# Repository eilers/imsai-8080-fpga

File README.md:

# S-100 compatible Computer

This project contains a full S-100 bus compliant micro computer based on the IMSAI-8080 design (which is basically a clone of the Altair 8800).
But instead of using old and hard to find computer parts, we use FPGAs to emulate their behavior.

**Please note:** This project is work in process! So please do not expect anything working for now.

This project contains the following components:

## S-100 Backplane (Motherboard)

The PCB here was not tested or used. I just ordered the board from [SmallRun](https://smallrun.net/shop/retrodisks/9-slot-s100-motherboard-with-integrated-power).
The Source of this version can be found on [GitHub](https://github.com/nullvalue0/S100MotherboardV5)

See folder `./S100MotherboardV5`

## S-100 Front Panel (CP-A)

This was also taken from [s100Computers](https://www.s100computers.com/My%20System%20Pages/FP%20Board/FP%20Board.htm) and cleaned to work with KiCad V10.

See folder `./S100-front-panel`

**Note:** This is not the design of the original CP-A provided by IMSAI in 1975. This one confirms the IEEE 696 and therefore works a bit different.

## IMSAI Front Panel (CP-A)

This is created from the original schmatics by IMSAI MPU-A REV.A 2/76.
In order to get a working reference, I decided to order the full front panel from [parastream.com](https://www.parastream.com/imsai/boards/cp-a-r.aspx) that belongs to the design here.

Important: This design is not fully IEEE 696 compatible without modifications as documented on the web page. Our Bus Master board is compatible to IMSAI and IEEE 696 if you select the correct FPGA core for it.

See folder `./imsai_cp-a`

## Bus Master

This is my work. The idea is to use only level shifters in order to connect a FPGA directly to the S-100 bus. All kind of S-100 boards that behave as bus master can therefore be recreated just be replacing the FPGA code. The first approach is to run a full IMSAI CPU board (MPU-A) on this board.
This board uses the [TE0725-04-21C-1-A](https://www.trenz-electronic.de/de/FPGA-Modul-mit-AMD-Artix-7A15T-1C-2-x-50-Pin-Header-3-5-x-7-3-cm/TE0725-04-21C-1-A) from Trenz, based on the AMD Artix™ 7A15T-1C.

See folder `./s100-bus-master`

The first FPGA implementation can be found in the folder `./s100-bus-master-fpga`. This code only contains some test code for debugging the S100 bus.

## References

* https://www.s100computers.com/index.html
* https://www.retrotechnology.com/herbs_stuff/s100.html
* https://github.com/nullvalue0/S100MotherboardV5

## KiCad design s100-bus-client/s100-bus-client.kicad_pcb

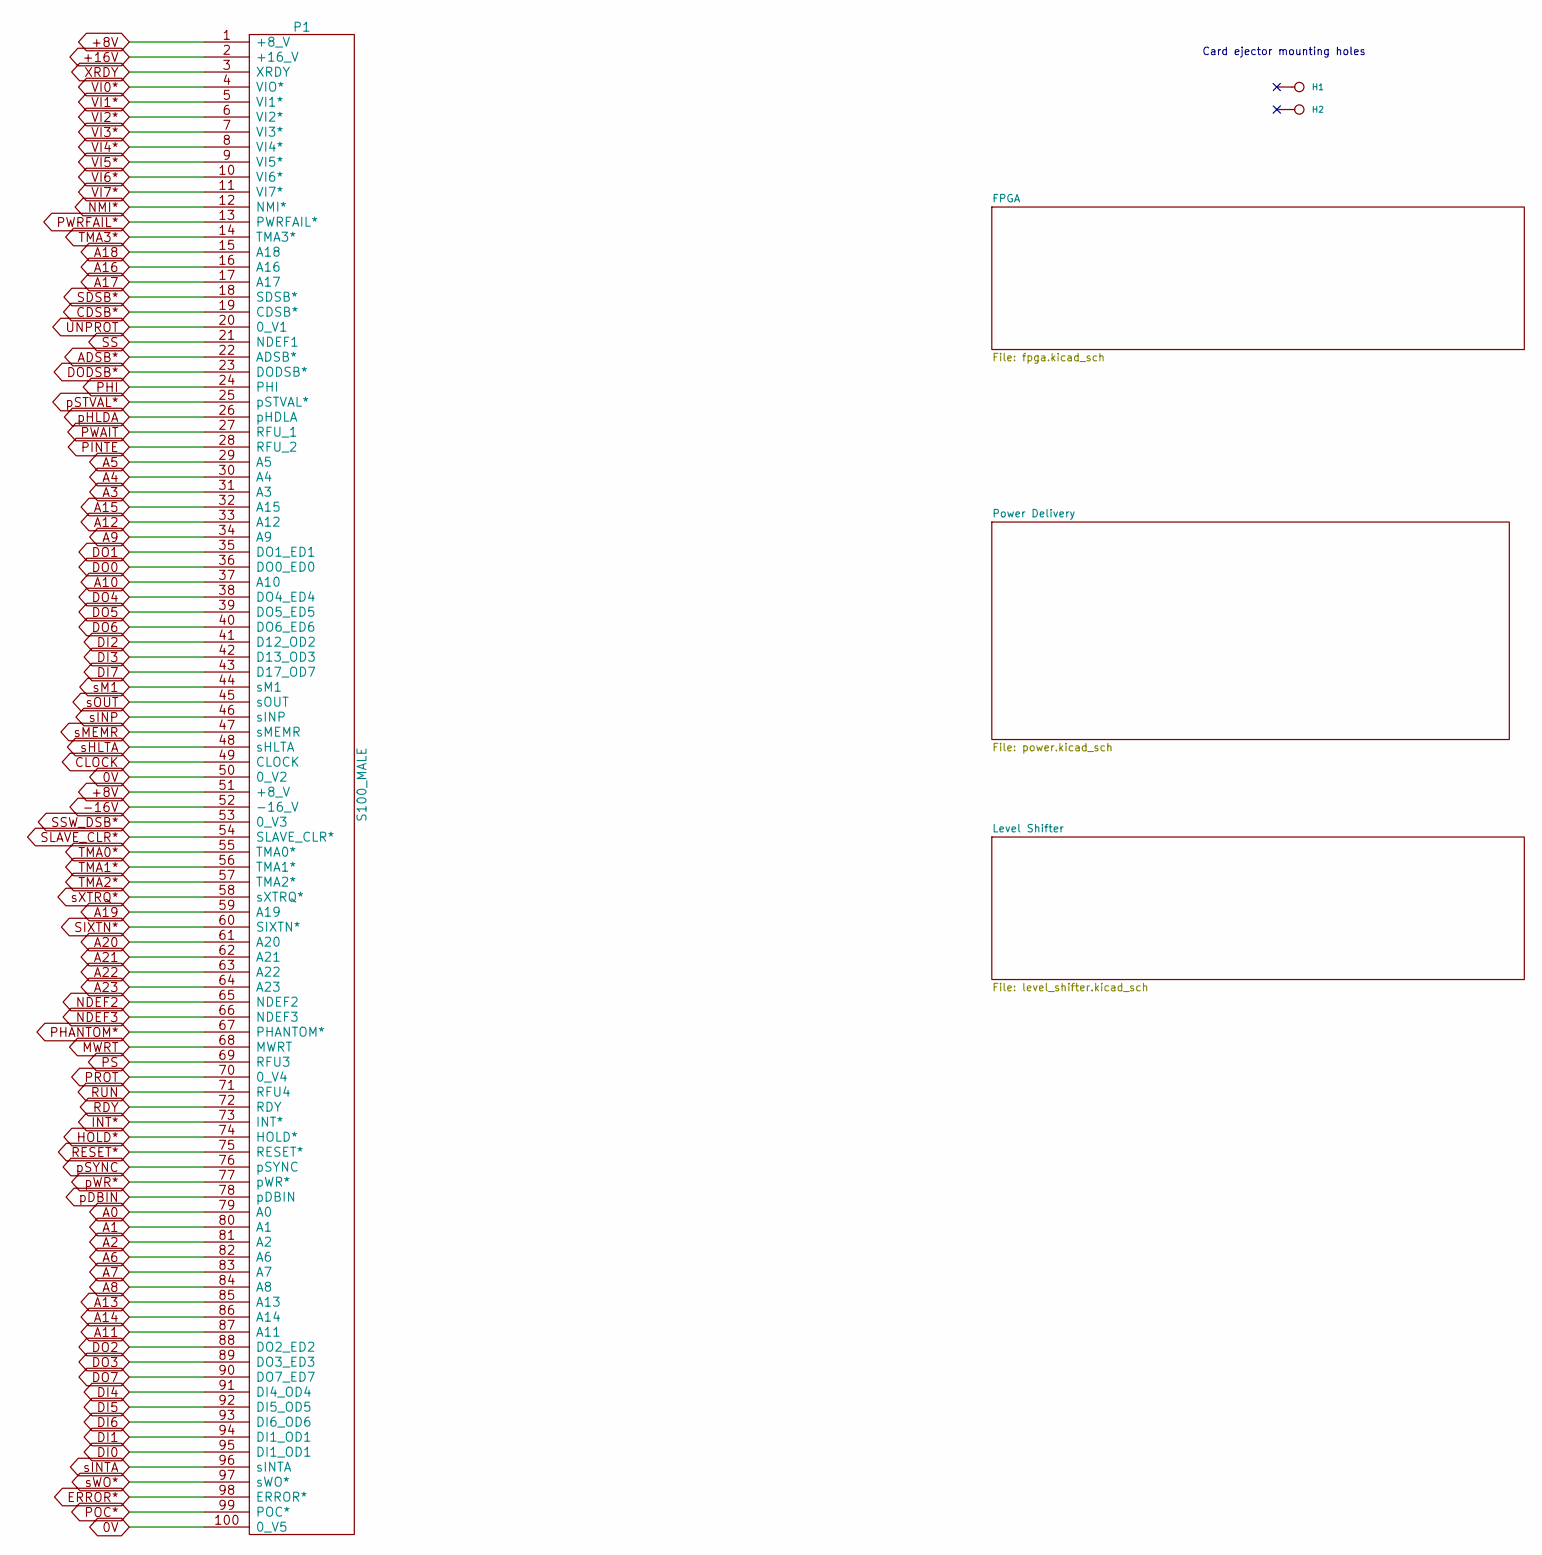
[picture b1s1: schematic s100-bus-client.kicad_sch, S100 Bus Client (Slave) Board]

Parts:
H1, H2: Ejector; s100-ejector
P1: S100_MALE; s100-edge-connector-male

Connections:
0V: P1.50 (0_V2), P1.100 (0_V5); also elsewhere on the board
+8V: P1.1 (+8_V), P1.51 (+8_V); also elsewhere on the board
+16V: P1.2 (+16_V)
-16V: P1.52 (-16_V)
A0: P1.79 (A0); also elsewhere on the board
A1: P1.80 (A1); also elsewhere on the board
A2: P1.81 (A2); also elsewhere on the board
A3: P1.31 (A3); also elsewhere on the board
A4: P1.30 (A4); also elsewhere on the board
A5: P1.29 (A5); also elsewhere on the board
A6: P1.82 (A6); also elsewhere on the board
A7: P1.83 (A7); also elsewhere on the board
A8: P1.84 (A8); also elsewhere on the board
A9: P1.34 (A9); also elsewhere on the board
A10: P1.37 (A10); also elsewhere on the board
A11: P1.87 (A11); also elsewhere on the board
A12: P1.33 (A12); also elsewhere on the board
A13: P1.85 (A13); also elsewhere on the board
A14: P1.86 (A14); also elsewhere on the board
A15: P1.32 (A15); also elsewhere on the board
A16: P1.16 (A16); also elsewhere on the board
A17: P1.17 (A17); also elsewhere on the board
A18: P1.15 (A18); also elsewhere on the board
A19: P1.59 (A19); also elsewhere on the board
A20: P1.61 (A20); also elsewhere on the board
A21: P1.62 (A21); also elsewhere on the board
A22: P1.63 (A22); also elsewhere on the board
A23: P1.64 (A23); also elsewhere on the board
ADSB*: P1.22 (ADSB*)
CDSB*: P1.19 (CDSB*)
CLOCK: P1.49 (CLOCK)
DI0: P1.95 (DI1_OD1); also elsewhere on the board
DI1: P1.94 (DI1_OD1); also elsewhere on the board
DI2: P1.41 (D12_OD2); also elsewhere on the board
DI3: P1.42 (D13_OD3); also elsewhere on the board
DI4: P1.91 (DI4_OD4); also elsewhere on the board
DI5: P1.92 (DI5_OD5); also elsewhere on the board
DI6: P1.93 (DI6_OD6); also elsewhere on the board
DI7: P1.43 (D17_OD7); also elsewhere on the board
DO0: P1.36 (DO0_ED0); also elsewhere on the board
DO1: P1.35 (DO1_ED1); also elsewhere on the board
DO2: P1.88 (DO2_ED2); also elsewhere on the board
DO3: P1.89 (DO3_ED3); also elsewhere on the board
DO4: P1.38 (DO4_ED4); also elsewhere on the board
DO5: P1.39 (DO5_ED5); also elsewhere on the board
DO6: P1.40 (DO6_ED6); also elsewhere on the board
DO7: P1.90 (DO7_ED7); also elsewhere on the board
DODSB*: P1.23 (DODSB*)
ERROR*: P1.98 (ERROR*)
HOLD*: P1.74 (HOLD*)
INT*: P1.73 (INT*)
MWRT: P1.68 (MWRT)
NDEF2: P1.65 (NDEF2)
NDEF3: P1.66 (NDEF3)
NMI*: P1.12 (NMI*)
PHANTOM*: P1.67 (PHANTOM*)
PHI: P1.24 (PHI)
PINTE: P1.28 (RFU_2)
POC*: P1.99 (POC*); also elsewhere on the board
PROT: P1.70 (0_V4)
PS: P1.69 (RFU3)
PWAIT: P1.27 (RFU_1)
PWRFAIL*: P1.13 (PWRFAIL*)
RDY: P1.72 (RDY)
RESET*: P1.75 (RESET*); also elsewhere on the board
RUN: P1.71 (RFU4)
SDSB*: P1.18 (SDSB*)
SIXTN*: P1.60 (SIXTN*)
SLAVE_CLR*: P1.54 (SLAVE_CLR*)
SS: P1.21 (NDEF1)
SSW_DSB*: P1.53 (0_V3)
TMA0*: P1.55 (TMA0*)
TMA1*: P1.56 (TMA1*)
TMA2*: P1.57 (TMA2*)
TMA3*: P1.14 (TMA3*)
UNPROT: P1.20 (0_V1)
VI0*: P1.4 (VIO*)
VI1*: P1.5 (VI1*)
VI2*: P1.6 (VI2*)
VI3*: P1.7 (VI3*)
VI4*: P1.8 (VI4*)
VI5*: P1.9 (VI5*)
VI6*: P1.10 (VI6*)
VI7*: P1.11 (VI7*)
XRDY: P1.3 (XRDY)
pDBIN: P1.78 (pDBIN); also elsewhere on the board
pHLDA: P1.26 (pHDLA)
pSTVAL*: P1.25 (pSTVAL*)
pSYNC: P1.76 (pSYNC)
pWR*: P1.77 (pWR*); also elsewhere on the board
sHLTA: P1.48 (sHLTA)
sINP: P1.46 (sINP)
sINTA: P1.96 (sINTA)
sM1: P1.44 (sM1)
sMEMR: P1.47 (sMEMR); also elsewhere on the board
sOUT: P1.45 (sOUT); also elsewhere on the board
sWO*: P1.97 (sWO*)
sXTRQ*: P1.58 (sXTRQ*)

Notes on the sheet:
Card ejector mounting holes

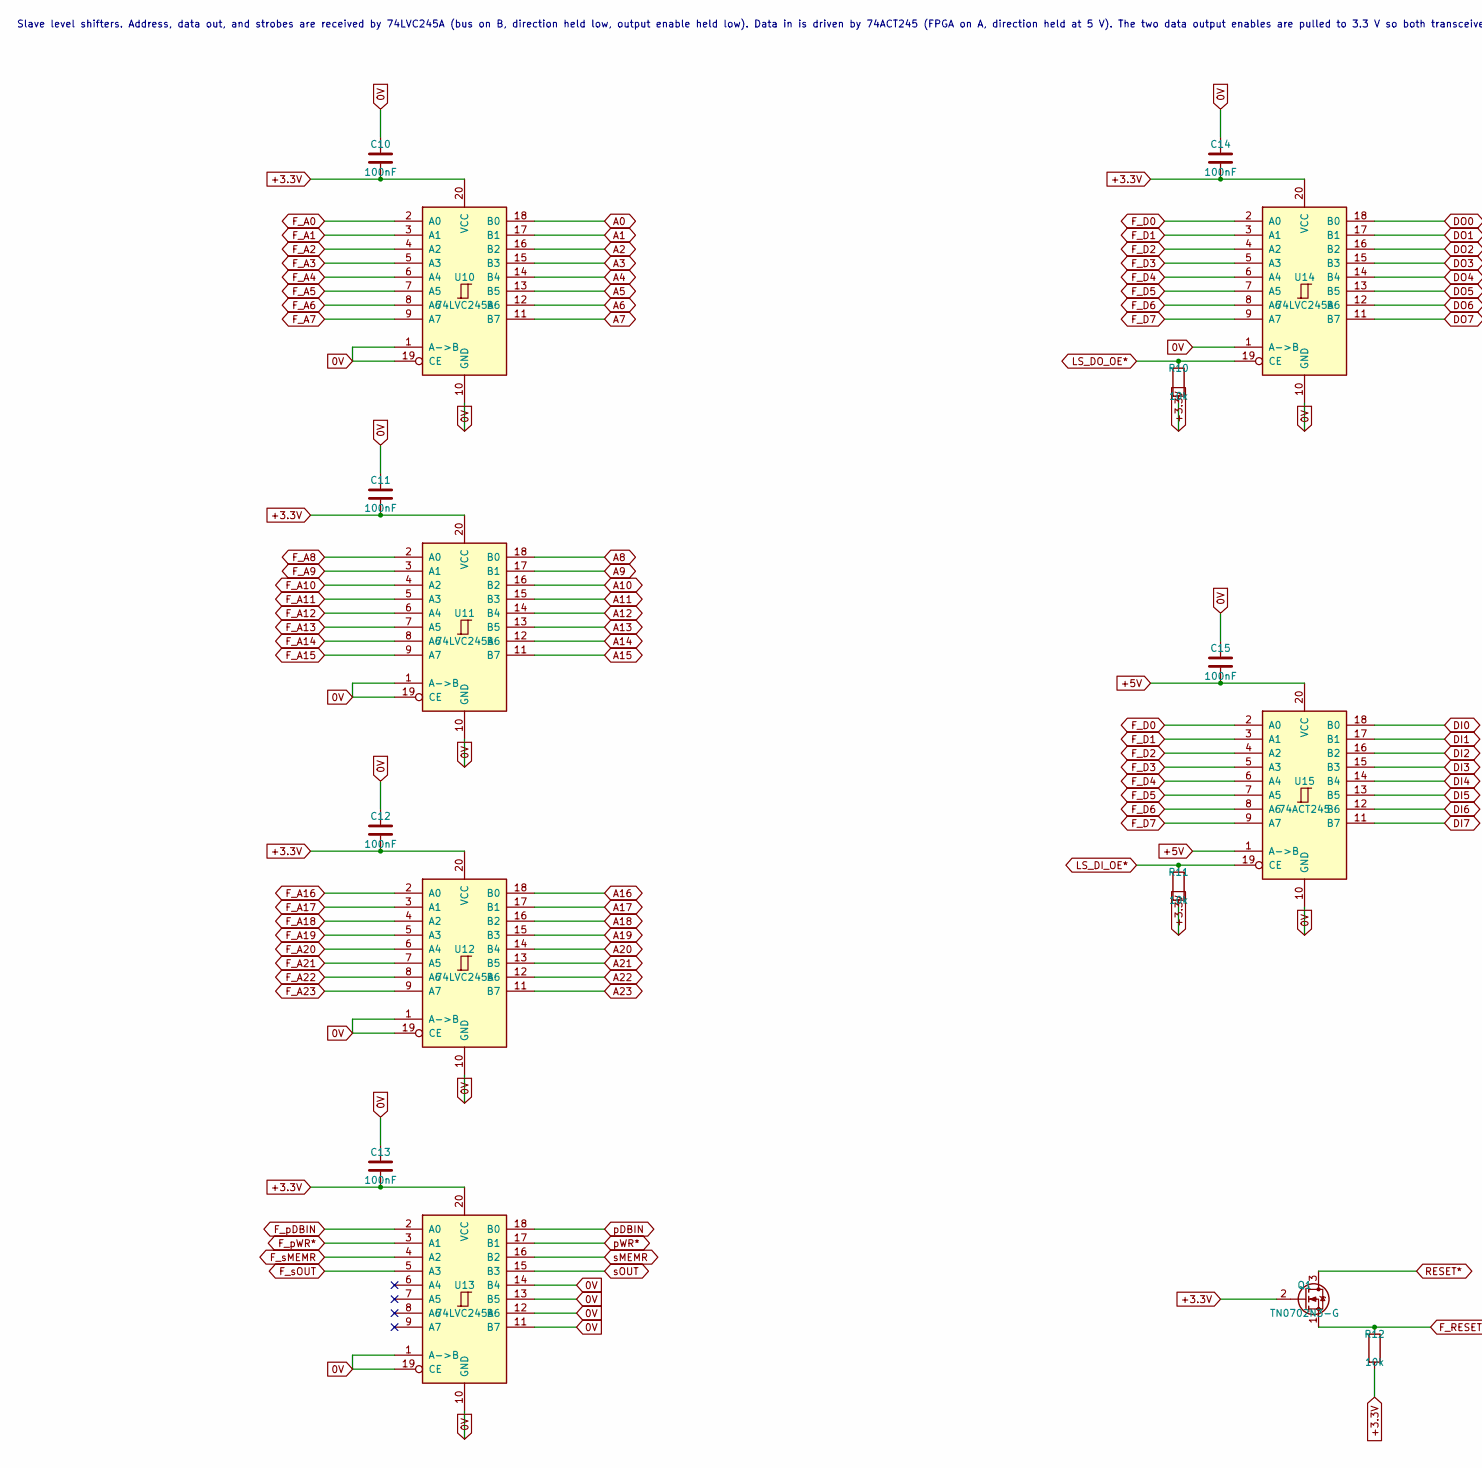
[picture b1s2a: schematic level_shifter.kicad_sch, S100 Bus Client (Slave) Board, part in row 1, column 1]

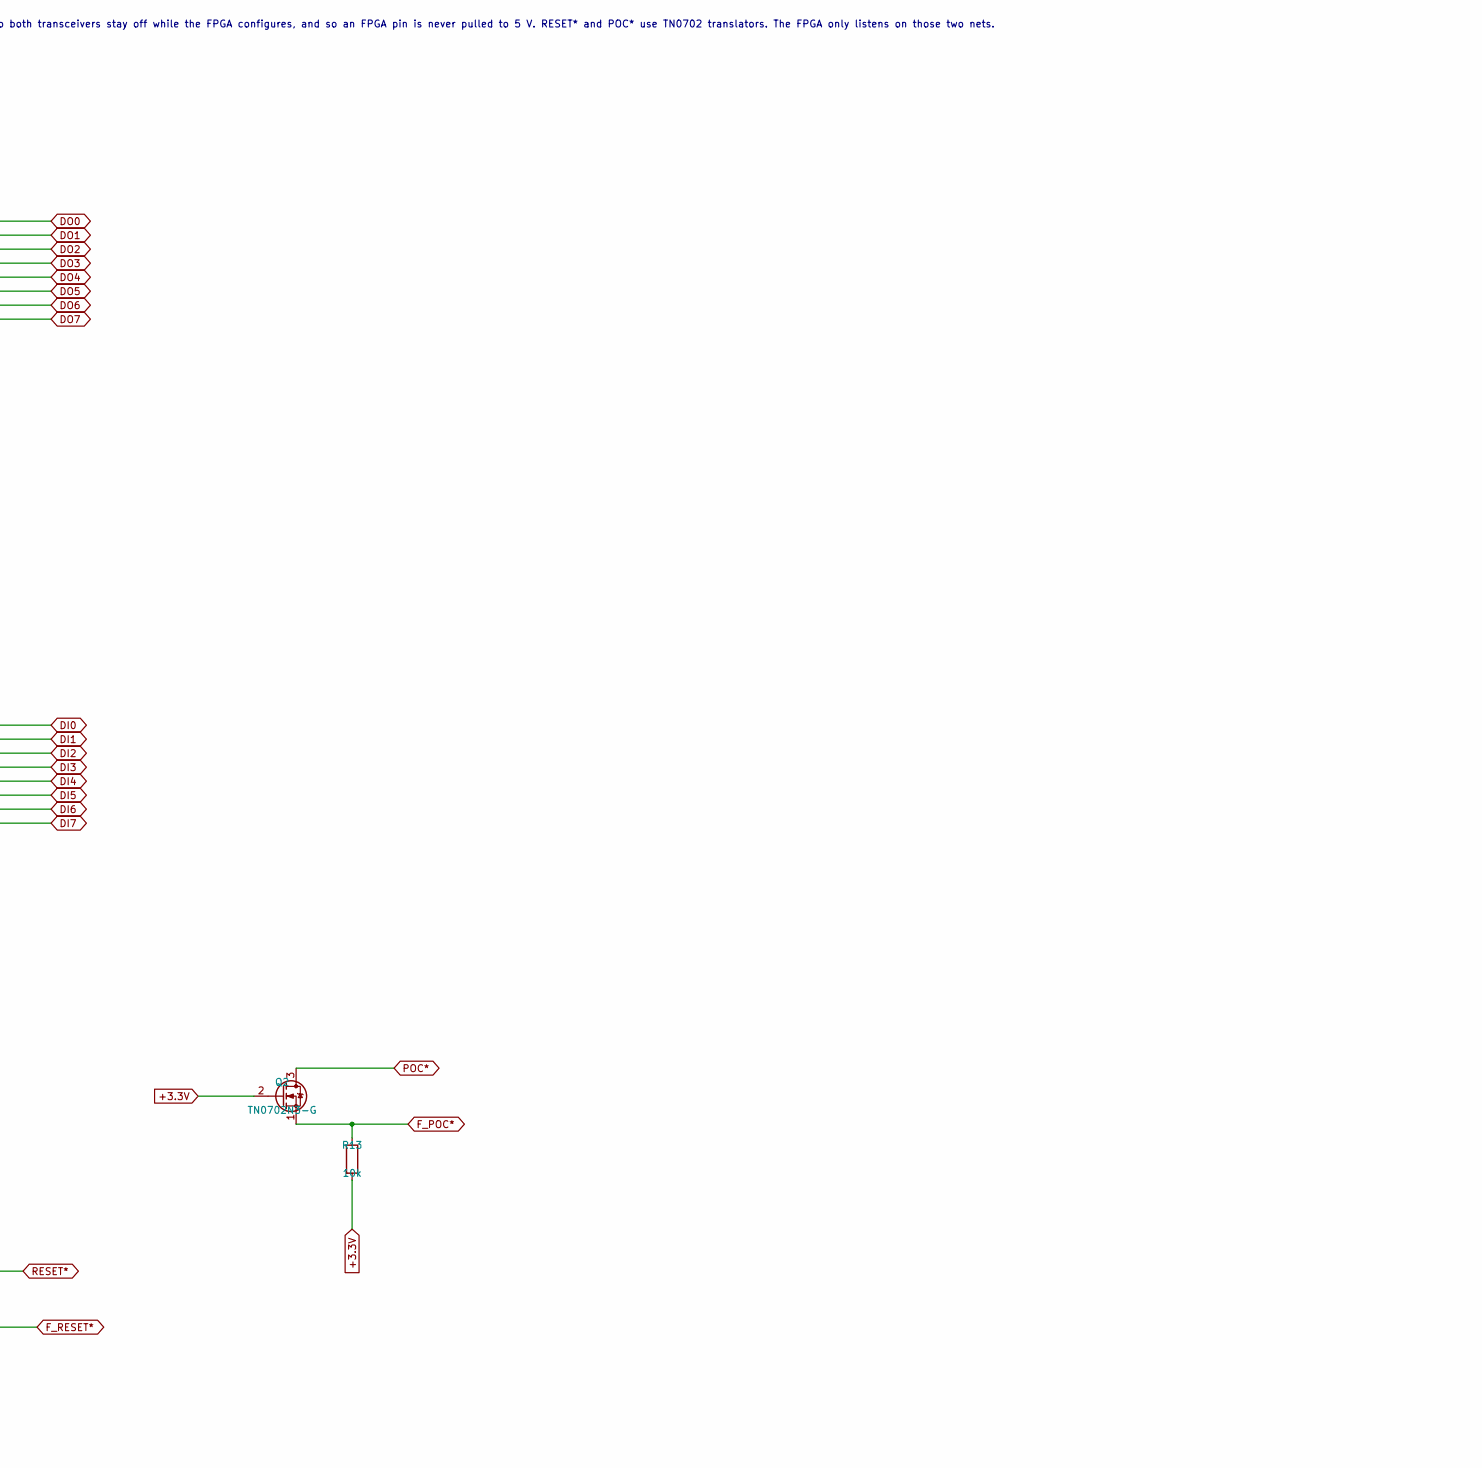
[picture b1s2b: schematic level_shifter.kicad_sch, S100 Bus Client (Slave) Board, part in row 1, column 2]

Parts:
C10, C11, C12, C13, C14, C15: 100nF; C_Disc_D5.0mm_W2.5mm_P5.00mm
Q1, Q2: TN0702N3-G; TO-92
R10, R11, R12, R13: 10k; R_Axial_DIN0207_L6.3mm_D2.5mm_P10.16mm_Horizontal
U10, U11, U12, U13, U14: 74LVC245A; DIP-20_W7.62mm
U15: 74ACT245; DIP-20_W7.62mm

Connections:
0V: C10.1, C11.1, C12.1, C13.1, C14.1, C15.1, U10.1 (A->B), U10.10 (GND), U10.19 (CE), U11.1 (A->B), U11.10 (GND), U11.19 (CE), U12.1 (A->B), U12.10 (GND), U12.19 (CE), U13.1 (A->B), U13.10 (GND), U13.11 (B7), U13.12 (B6), U13.13 (B5), U13.14 (B4), U13.19 (CE), U14.1 (A->B), U14.10 (GND), U15.10 (GND); also elsewhere on the board
+3.3V: C10.2, C11.2, C12.2, C13.2, C14.2, Q1.2 (G), Q2.2 (G), R10.2, R11.2, R12.2, R13.2, U10.20 (VCC), U11.20 (VCC), U12.20 (VCC), U13.20 (VCC), U14.20 (VCC); also elsewhere on the board
+5V: C15.2, U15.1 (A->B), U15.20 (VCC); also elsewhere on the board
A0: U10.18 (B0); also elsewhere on the board
A1: U10.17 (B1); also elsewhere on the board
A2: U10.16 (B2); also elsewhere on the board
A3: U10.15 (B3); also elsewhere on the board
A4: U10.14 (B4); also elsewhere on the board
A5: U10.13 (B5); also elsewhere on the board
A6: U10.12 (B6); also elsewhere on the board
A7: U10.11 (B7); also elsewhere on the board
A8: U11.18 (B0); also elsewhere on the board
A9: U11.17 (B1); also elsewhere on the board
A10: U11.16 (B2); also elsewhere on the board
A11: U11.15 (B3); also elsewhere on the board
A12: U11.14 (B4); also elsewhere on the board
A13: U11.13 (B5); also elsewhere on the board
A14: U11.12 (B6); also elsewhere on the board
A15: U11.11 (B7); also elsewhere on the board
A16: U12.18 (B0); also elsewhere on the board
A17: U12.17 (B1); also elsewhere on the board
A18: U12.16 (B2); also elsewhere on the board
A19: U12.15 (B3); also elsewhere on the board
A20: U12.14 (B4); also elsewhere on the board
A21: U12.13 (B5); also elsewhere on the board
A22: U12.12 (B6); also elsewhere on the board
A23: U12.11 (B7); also elsewhere on the board
DI0: U15.18 (B0); also elsewhere on the board
DI1: U15.17 (B1); also elsewhere on the board
DI2: U15.16 (B2); also elsewhere on the board
DI3: U15.15 (B3); also elsewhere on the board
DI4: U15.14 (B4); also elsewhere on the board
DI5: U15.13 (B5); also elsewhere on the board
DI6: U15.12 (B6); also elsewhere on the board
DI7: U15.11 (B7); also elsewhere on the board
DO0: U14.18 (B0); also elsewhere on the board
DO1: U14.17 (B1); also elsewhere on the board
DO2: U14.16 (B2); also elsewhere on the board
DO3: U14.15 (B3); also elsewhere on the board
DO4: U14.14 (B4); also elsewhere on the board
DO5: U14.13 (B5); also elsewhere on the board
DO6: U14.12 (B6); also elsewhere on the board
DO7: U14.11 (B7); also elsewhere on the board
F_A0: U10.2 (A0); also elsewhere on the board
F_A1: U10.3 (A1); also elsewhere on the board
F_A2: U10.4 (A2); also elsewhere on the board
F_A3: U10.5 (A3); also elsewhere on the board
F_A4: U10.6 (A4); also elsewhere on the board
F_A5: U10.7 (A5); also elsewhere on the board
F_A6: U10.8 (A6); also elsewhere on the board
F_A7: U10.9 (A7); also elsewhere on the board
F_A8: U11.2 (A0); also elsewhere on the board
F_A9: U11.3 (A1); also elsewhere on the board
F_A10: U11.4 (A2); also elsewhere on the board
F_A11: U11.5 (A3); also elsewhere on the board
F_A12: U11.6 (A4); also elsewhere on the board
F_A13: U11.7 (A5); also elsewhere on the board
F_A14: U11.8 (A6); also elsewhere on the board
F_A15: U11.9 (A7); also elsewhere on the board
F_A16: U12.2 (A0); also elsewhere on the board
F_A17: U12.3 (A1); also elsewhere on the board
F_A18: U12.4 (A2); also elsewhere on the board
F_A19: U12.5 (A3); also elsewhere on the board
F_A20: U12.6 (A4); also elsewhere on the board
F_A21: U12.7 (A5); also elsewhere on the board
F_A22: U12.8 (A6); also elsewhere on the board
F_A23: U12.9 (A7); also elsewhere on the board
F_D0: U14.2 (A0), U15.2 (A0); also elsewhere on the board
F_D1: U14.3 (A1), U15.3 (A1); also elsewhere on the board
F_D2: U14.4 (A2), U15.4 (A2); also elsewhere on the board
F_D3: U14.5 (A3), U15.5 (A3); also elsewhere on the board
F_D4: U14.6 (A4), U15.6 (A4); also elsewhere on the board
F_D5: U14.7 (A5), U15.7 (A5); also elsewhere on the board
F_D6: U14.8 (A6), U15.8 (A6); also elsewhere on the board
F_D7: U14.9 (A7), U15.9 (A7); also elsewhere on the board
F_POC*: Q2.1 (S), R13.1; also elsewhere on the board
F_RESET*: Q1.1 (S), R12.1; also elsewhere on the board
F_pDBIN: U13.2 (A0); also elsewhere on the board
F_pWR*: U13.3 (A1); also elsewhere on the board
F_sMEMR: U13.4 (A2); also elsewhere on the board
F_sOUT: U13.5 (A3); also elsewhere on the board
LS_DI_OE*: R11.1, U15.19 (CE); also elsewhere on the board
LS_DO_OE*: R10.1, U14.19 (CE); also elsewhere on the board
POC*: Q2.3 (D); also elsewhere on the board
RESET*: Q1.3 (D); also elsewhere on the board
pDBIN: U13.18 (B0); also elsewhere on the board
pWR*: U13.17 (B1); also elsewhere on the board
sMEMR: U13.16 (B2); also elsewhere on the board
sOUT: U13.15 (B3); also elsewhere on the board

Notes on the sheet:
Slave level shifters. Address, data out, and strobes are received by 74LVC245A (bus on B, direction held low, output enable held low). Data in is driven by 74ACT245 (FPGA on A, direction held at 5 V). The two data output enables are pulled to 3.3 V so both transceivers stay off while the FPGA confi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

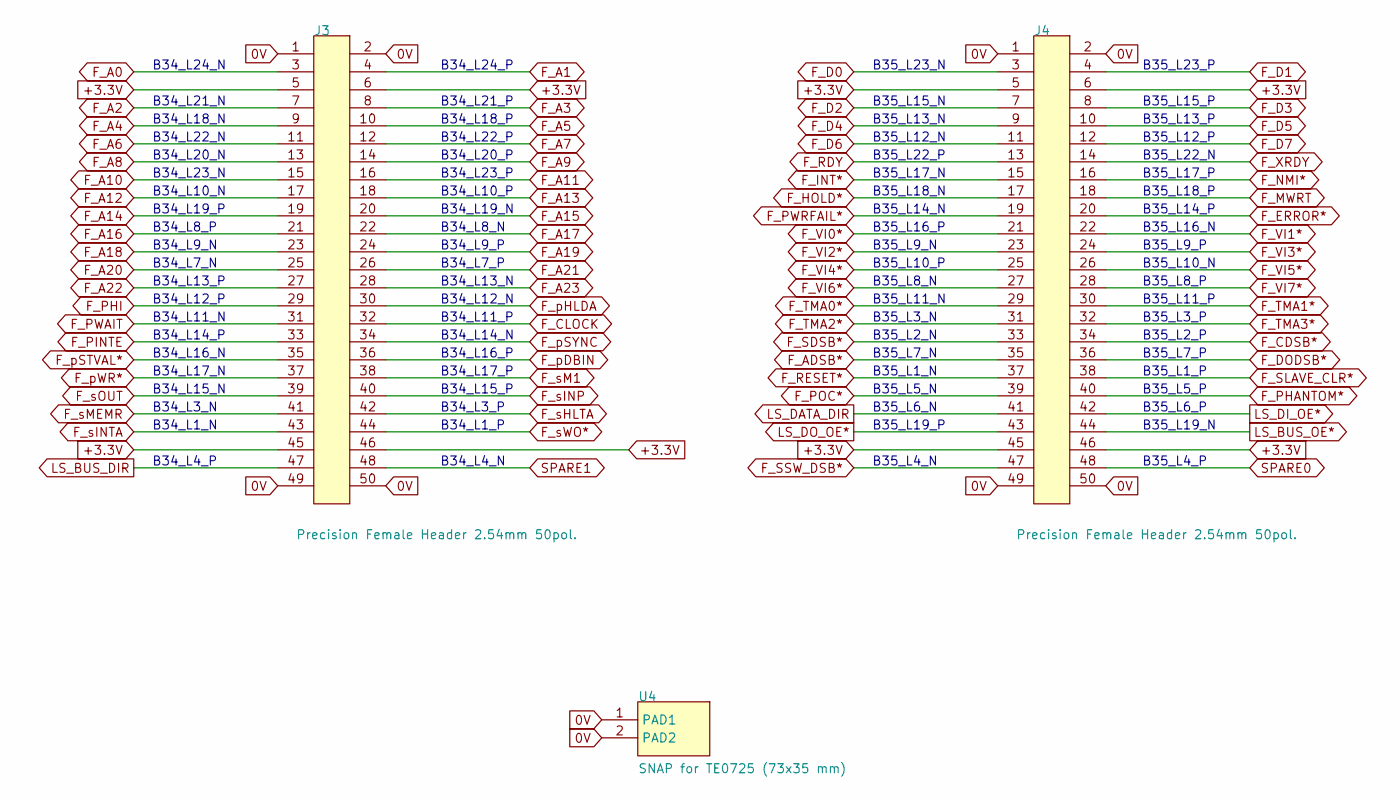
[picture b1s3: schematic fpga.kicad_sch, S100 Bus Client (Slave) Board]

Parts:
J3, J4: Precision Female Header 2.54mm 50pol.; PinSocket_2x25_TE_North
U4: SNAP for TE0725 (73x35 mm); TE0725_Snap

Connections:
0V: J3.1, J3.2, J3.49, J3.50, J4.1, J4.2, J4.49, J4.50, U4.1, U4.2; also elsewhere on the board
+3.3V: J3.5, J3.6, J3.45, J3.46, J4.5, J4.6, J4.45, J4.46; also elsewhere on the board
F_A0: J3.3; also elsewhere on the board
F_A1: J3.4; also elsewhere on the board
F_A2: J3.7; also elsewhere on the board
F_A3: J3.8; also elsewhere on the board
F_A4: J3.9; also elsewhere on the board
F_A5: J3.10; also elsewhere on the board
F_A6: J3.11; also elsewhere on the board
F_A7: J3.12; also elsewhere on the board
F_A8: J3.13; also elsewhere on the board
F_A9: J3.14; also elsewhere on the board
F_A10: J3.15; also elsewhere on the board
F_A11: J3.16; also elsewhere on the board
F_A12: J3.17; also elsewhere on the board
F_A13: J3.18; also elsewhere on the board
F_A14: J3.19; also elsewhere on the board
F_A15: J3.20; also elsewhere on the board
F_A16: J3.21; also elsewhere on the board
F_A17: J3.22; also elsewhere on the board
F_A18: J3.23; also elsewhere on the board
F_A19: J3.24; also elsewhere on the board
F_A20: J3.25; also elsewhere on the board
F_A21: J3.26; also elsewhere on the board
F_A22: J3.27; also elsewhere on the board
F_A23: J3.28; also elsewhere on the board
F_ADSB*: J4.35
F_CDSB*: J4.34
F_CLOCK: J3.32
F_D0: J4.3; also elsewhere on the board
F_D1: J4.4; also elsewhere on the board
F_D2: J4.7; also elsewhere on the board
F_D3: J4.8; also elsewhere on the board
F_D4: J4.9; also elsewhere on the board
F_D5: J4.10; also elsewhere on the board
F_D6: J4.11; also elsewhere on the board
F_D7: J4.12; also elsewhere on the board
F_DODSB*: J4.36
F_ERROR*: J4.20
F_HOLD*: J4.17
F_INT*: J4.15
F_MWRT: J4.18
F_NMI*: J4.16
F_PHANTOM*: J4.40
F_PHI: J3.29
F_PINTE: J3.33
F_POC*: J4.39; also elsewhere on the board
F_PWAIT: J3.31
F_PWRFAIL*: J4.19
F_RDY: J4.13
F_RESET*: J4.37; also elsewhere on the board
F_SDSB*: J4.33
F_SLAVE_CLR*: J4.38
F_SSW_DSB*: J4.47
F_TMA0*: J4.29
F_TMA1*: J4.30
F_TMA2*: J4.31
F_TMA3*: J4.32
F_VI0*: J4.21
F_VI1*: J4.22
F_VI2*: J4.23
F_VI3*: J4.24
F_VI4*: J4.25
F_VI5*: J4.26
F_VI6*: J4.27
F_VI7*: J4.28
F_XRDY: J4.14
F_pDBIN: J3.36; also elsewhere on the board
F_pHLDA: J3.30
F_pSTVAL*: J3.35
F_pSYNC: J3.34
F_pWR*: J3.37; also elsewhere on the board
F_sHLTA: J3.42
F_sINP: J3.40
F_sINTA: J3.43
F_sM1: J3.38
F_sMEMR: J3.41; also elsewhere on the board
F_sOUT: J3.39; also elsewhere on the board
F_sWO*: J3.44
LS_BUS_DIR: J3.47
LS_BUS_OE*: J4.44
LS_DATA_DIR: J4.41
LS_DI_OE*: J4.42; also elsewhere on the board
LS_DO_OE*: J4.43; also elsewhere on the board
SPARE0: J4.48
SPARE1: J3.48

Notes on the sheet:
B34_L8_N
B35_L18_P
B34_L15_N
B35_L14_P
B35_L6_N
B35_L6_P
B35_L22_P
B35_L13_P
B35_L17_N
B34_L1_P
B35_L22_N
B34_L12_P
B35_L15_P
B34_L13_N
B34_L16_P
B34_L11_N
B34_L18_P
B35_L9_N
B35_L4_P
B35_L14_N
B35_L8_P
B35_L4_N
B34_L21_P
B34_L16_N
B34_L3_N
B35_L16_N
B35_L17_P
B34_L24_N
B34_L14_N
B35_L12_N
B35_L9_P
B34_L9_P
B35_L7_P
B35_L10_N
B35_L23_N
B34_L10_N
B34_L3_P
B34_L10_P
B34_L22_P
B35_L11_N

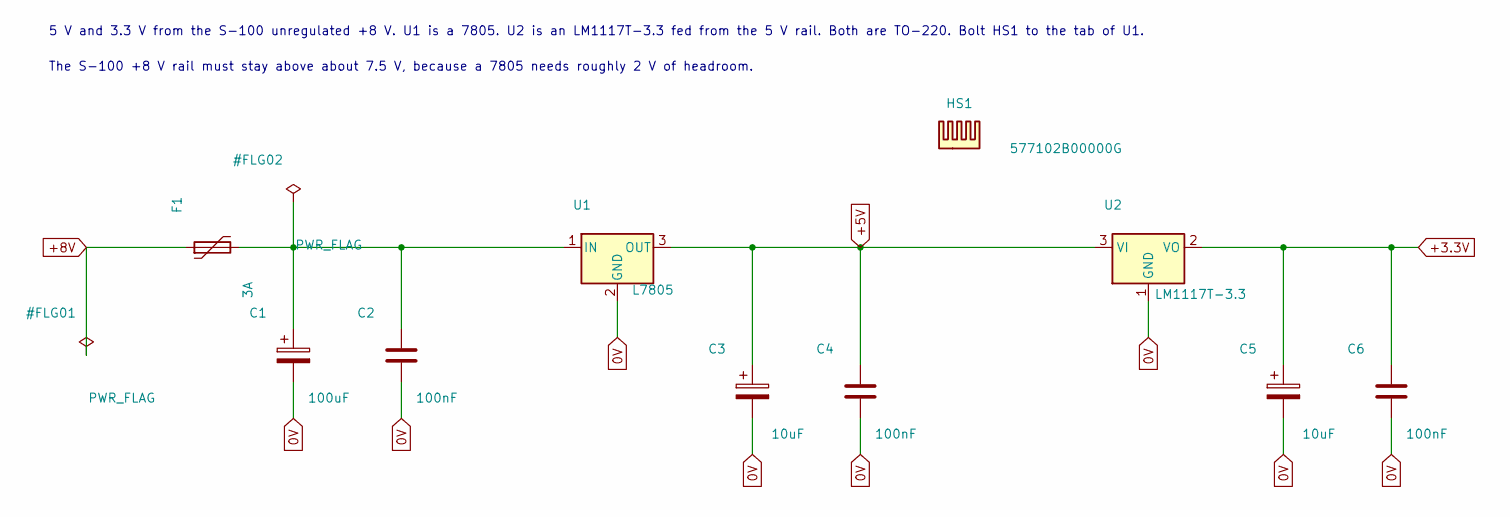
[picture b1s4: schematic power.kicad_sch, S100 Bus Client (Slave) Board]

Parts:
C1: 100uF; CP_Radial_D10.0mm_P5.00mm
C2, C4, C6: 100nF; C_Disc_D5.0mm_W2.5mm_P5.00mm
C3, C5: 10uF; CP_Radial_D6.3mm_P2.50mm
F1: 3A; Fuse_Bourns_MF-RHT300
HS1: 577102B00000G; MountingHole_3.2mm_M3
U1: L7805; TO-220-3_Vertical
U2: LM1117T-3.3; TO-220-3_Vertical

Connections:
0V: C1.2, C2.2, C3.2, C4.2, C5.2, C6.2, U1.2 (GND), U2.1 (GND); also elsewhere on the board
+3.3V: C5.1, C6.1, U2.2 (VO); also elsewhere on the board
+5V: C3.1, C4.1, U1.3 (OUT), U2.3 (VI); also elsewhere on the board
+8V: F1.1; also elsewhere on the board
unnamed: C1.1, C2.1, F1.2, U1.1 (IN)

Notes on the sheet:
The S-100 +8 V rail must stay above about 7.5 V, because a 7805 needs roughly 2 V of headroom.
5 V and 3.3 V from the S-100 unregulated +8 V. U1 is a 7805. U2 is an LM1117T-3.3 fed from the 5 V rail. Both are TO-220. Bolt HS1 to the tab of U1.

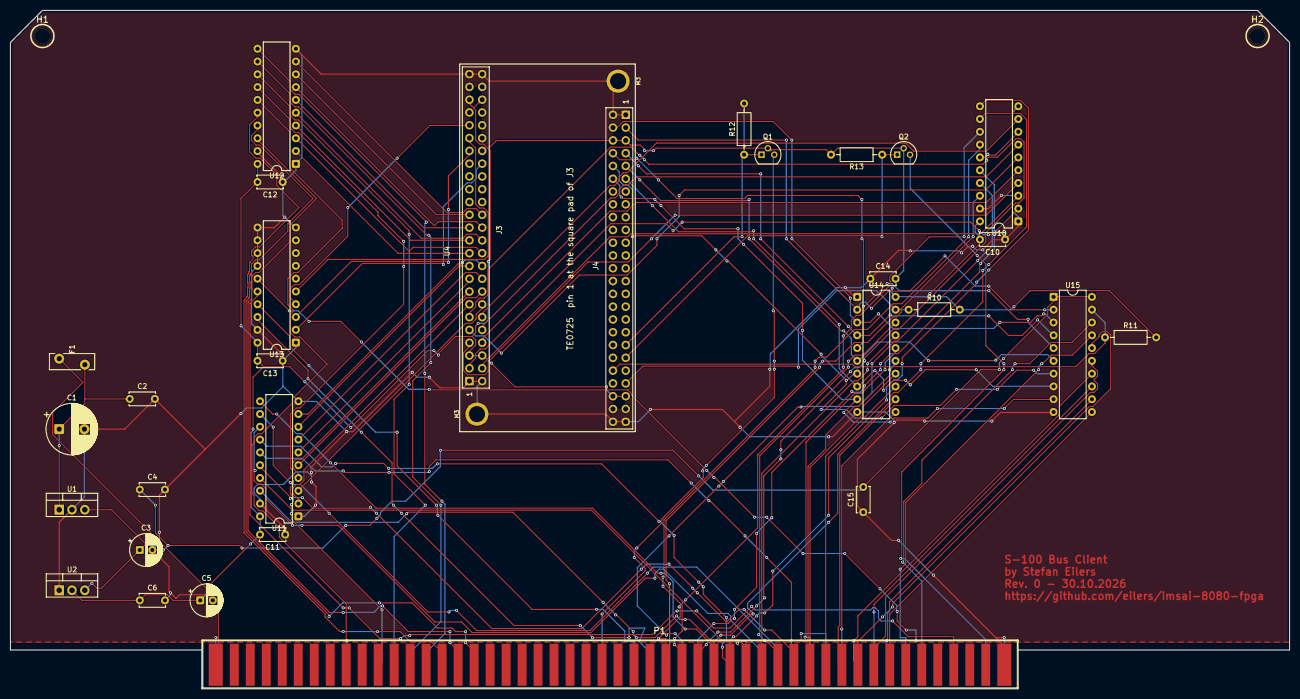
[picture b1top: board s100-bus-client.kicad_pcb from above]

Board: 2 copper layers, 254.0 x 134.6 mm, 33 parts (0 on the bottom side), 91 nets.

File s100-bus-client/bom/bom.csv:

Designator,Quantity,Value,Footprint,Package,MPN,DNP,Mount_Type,KiLib_Generator,Description,AN,MIXED,HELPURL,H-ART
C1,1,100uF,CP_Radial_D10.0mm_P5.00mm,,,,tht,capacitor/THT/other,,,,,
"C10, C11, C12, C13, C14, C15, C2, C4, C6",9,100nF,C_Disc_D5.0mm_W2.5mm_P5.00mm,,,,tht,capacitor/THT/other,Decoupling capacitor,,,,
"C3, C5",2,10uF,CP_Radial_D6.3mm_P2.50mm,,,,tht,capacitor/THT/other,,,,,
F1,1,3A,Fuse_Bourns_MF-RHT300,,,,tht,fuse,,,,,
"H1, H2",2,Ejector,s100-ejector,,,,tht,,,,,,
"J3, J4",2,Precision Female Header 2.54mm 50pol.,PinSocket_2x25_TE_North,,,,tht,,Buchsenleiste 2 reihig präz. 50pol.,28028,THT,B~{:}A~{D}adli~{b}datashee~{t}153,153-050-2-50-00
P1,1,S100_MALE,s100-edge-connector-male,,,,tht,,,,,,
"Q1, Q2",2,TN0702N3-G,TO-92,,,,tht,,"N-channel MOSFET, gate held at 3.3 V, FPGA listens only",,,,
"R10, R11, R12, R13",4,10k,R_Axial_DIN0207_L6.3mm_D2.5mm_P10.16mm_Horizontal,,,,tht,resistor/THT,Pull-up resistor,,,,
U1,1,L7805,TO-220-3_Vertical,,,,tht,package/TO_SOT/THT,,,,,
"U10, U11, U12, U13, U14",5,74LVC245A,DIP-20_W7.62mm,,,,tht,package/DIP/legacy,"[U10]Address A0-A7 receiver, bus B side to FPGA A side; [U11]Address A8-A15 receiver, bus B side to FPGA A side; [U12]Address A16-A23 receiver, bus B side to FPGA A side; [U13]Strobe receiver, bus B side to FPGA A side; [U14]Data-out receiver, bus DO on B, shared FPGA data on A",,,,
U15,1,74ACT245,DIP-20_W7.62mm,,,,tht,package/DIP/legacy,"Data-in driver, shared FPGA data on A, bus DI on B",,,,
U2,1,LM1117T-3.3,TO-220-3_Vertical,,,,tht,package/TO_SOT/THT,,,,,
U4,1,SNAP for TE0725 (73x35 mm),TE0725_Snap,,,,tht,,Snap for TE0725 (73x35mm),27270,SMT,,
